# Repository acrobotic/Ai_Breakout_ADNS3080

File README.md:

####Currently under development!

Overview
---
This repository includes the Eagle design files (schematics and layout) for our [ADNS3080 Brekout Board][1]. The ADNS3080 is an optical
mouse sensor with a 30x30 pixel resolution, 2000--6400 fps update rate, and SPI interface.

This breakout board provides the necessary circuitry to communicate with the sensor using a microcontroller via SPI (5V).  The board uses 
.1" spacing for easy mounting on a solderless breadboard. For more info on how to use the ADNS3080 optical mouse sensor for detecting optic flow please visit:
[http://learn.acrobotic.com/ADNS3080][2]

Product page
---
Please consider buying products from Acrobotic to help fund future Open-Source projects like this! We'll always put our best effort in every project, and release all our design files and code for you to use.

[Tutorials, technical details, and more information about this product can be found here: http://acrobotic.com/catalog/product/view/id/66][1]

We also [carry the standalone ADNS3080 chip in our store!][3]

License Information
---

All contents of this repository are licensed under a [Creative Commons Attribution-ShareAlike 3.0 Unported License](http://creativecommons.org/licenses/by-sa/3.0/).

[1]: http://acrobotic.com/catalog/product/view/id/66 "ADNS3080 Optical Mouse Sensor Breakout Board"
[2]: http://learn.acrobotic.com/ADNS3080 "Acrobotic ADNS3080 Tutorial"
[3]: http://acrobotic.com/catalog/product/view/id/65 "ADNS3080 Optical Mouses Sensor"

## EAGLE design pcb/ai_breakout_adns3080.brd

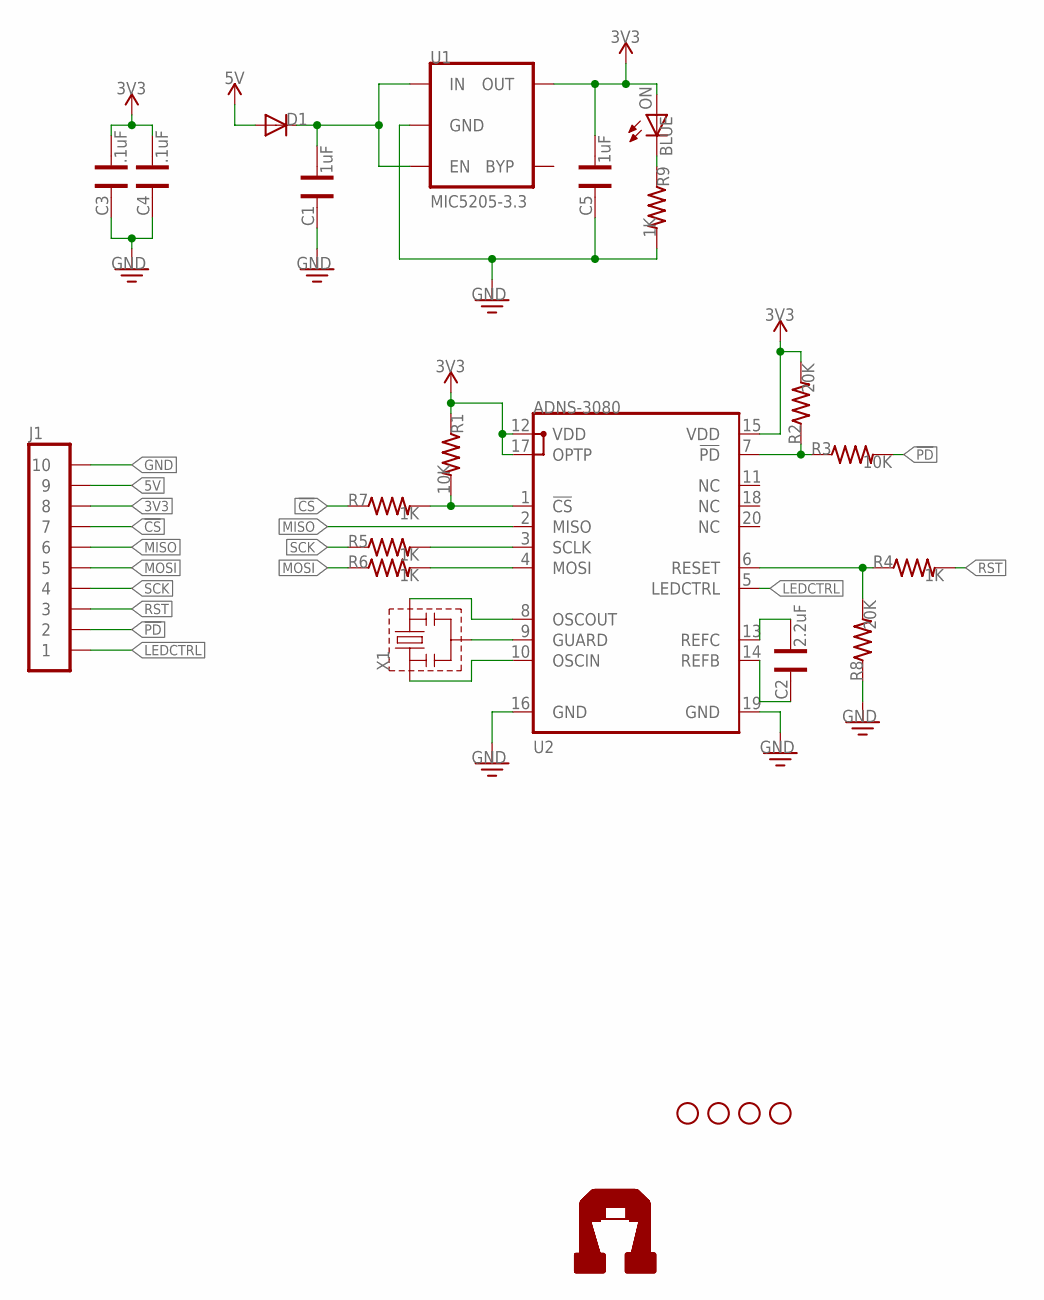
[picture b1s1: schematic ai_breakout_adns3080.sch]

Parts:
C1, C5: 1uF; CAP-0603
C2: 2.2uF; CAP-0603
C3, C4: .1uF; CAP-0603
D1: DIODESMA-403D; SMA-403D
J1: 1X10
ON: BLUE; LED-0603
R1, R3: 10K; RES-0603
R2, R8: 20K; RES-0603
R4, R5, R6, R7, R9: 1K; RES-0603
STANDOFF1, STANDOFF2, STANDOFF3, STANDOFF4: STAND-OFF
U1: MIC5205-3.3; SOT23-5
U2: ADNS-3080
U$2, U$3: AI-LOGOM; AI-LOGO-M
X1: RESON025X020; RESON-SMD-025X020

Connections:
3V3: C3.1, C4.1, C5.1, J1.8, ON.A, R1.1, R2.2, U1.5 (OUT), U2.12 (VDD), U2.15 (VDD), U2.17 (OPTP)
5V: D1.A, J1.9
!CS: J1.7, R7.1
!PD: J1.2, R3.2
GND: C1.2, C3.2, C4.2, C5.2, J1.10, R8.1, R9.2, U1.2 (GND), U2.16 (GND), U2.19 (GND)
LEDCTRL: J1.1, U2.5 (LEDCTRL)
MISO: J1.6, U2.2 (MISO)
MOSI: J1.5, R6.1
unnamed: C1.1, D1.C, U1.1 (IN), U1.3 (EN)
unnamed: U2.9 (GUARD), X1.2
unnamed: U2.8 (OSCOUT), X1.3
unnamed: R1.2, R7.2, U2.1 (!CS)
unnamed: R5.2, U2.3 (SCLK)
unnamed: U2.10 (OSCIN), X1.1
unnamed: R2.1, R3.1, U2.7 (!PD)
unnamed: R6.2, U2.4 (MOSI)
unnamed: R4.1, R8.2, U2.6 (RESET)
unnamed: C2.1, U2.13 (REFC)
unnamed: C2.2, U2.14 (REFB)
unnamed: ON.C, R9.1
RST: J1.3, R4.2
SCK: J1.4, R5.1

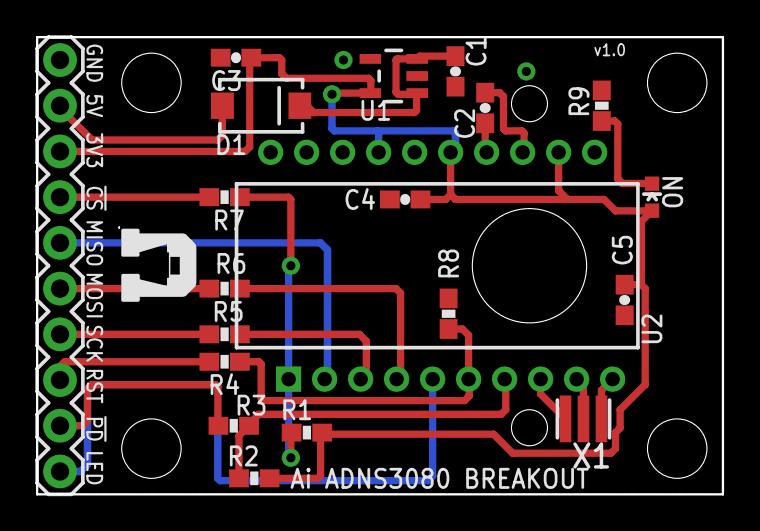
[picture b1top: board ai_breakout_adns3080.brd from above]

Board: 2 copper layers, 38.1 x 25.4 mm, 26 parts (1 on the bottom side), 22 nets.

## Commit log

2013-09-22 changes to the silkscreen. added gerbers.
2013-10-12 Revised version. Finished BOM.
2013-10-12 First commit to pages branch
2013-10-12 Fixed typo in the description
2013-10-12 Fixed typo in the README file
2013-10-12 Modified part number in BOM
2013-11-26 updating to use the latest libraries
